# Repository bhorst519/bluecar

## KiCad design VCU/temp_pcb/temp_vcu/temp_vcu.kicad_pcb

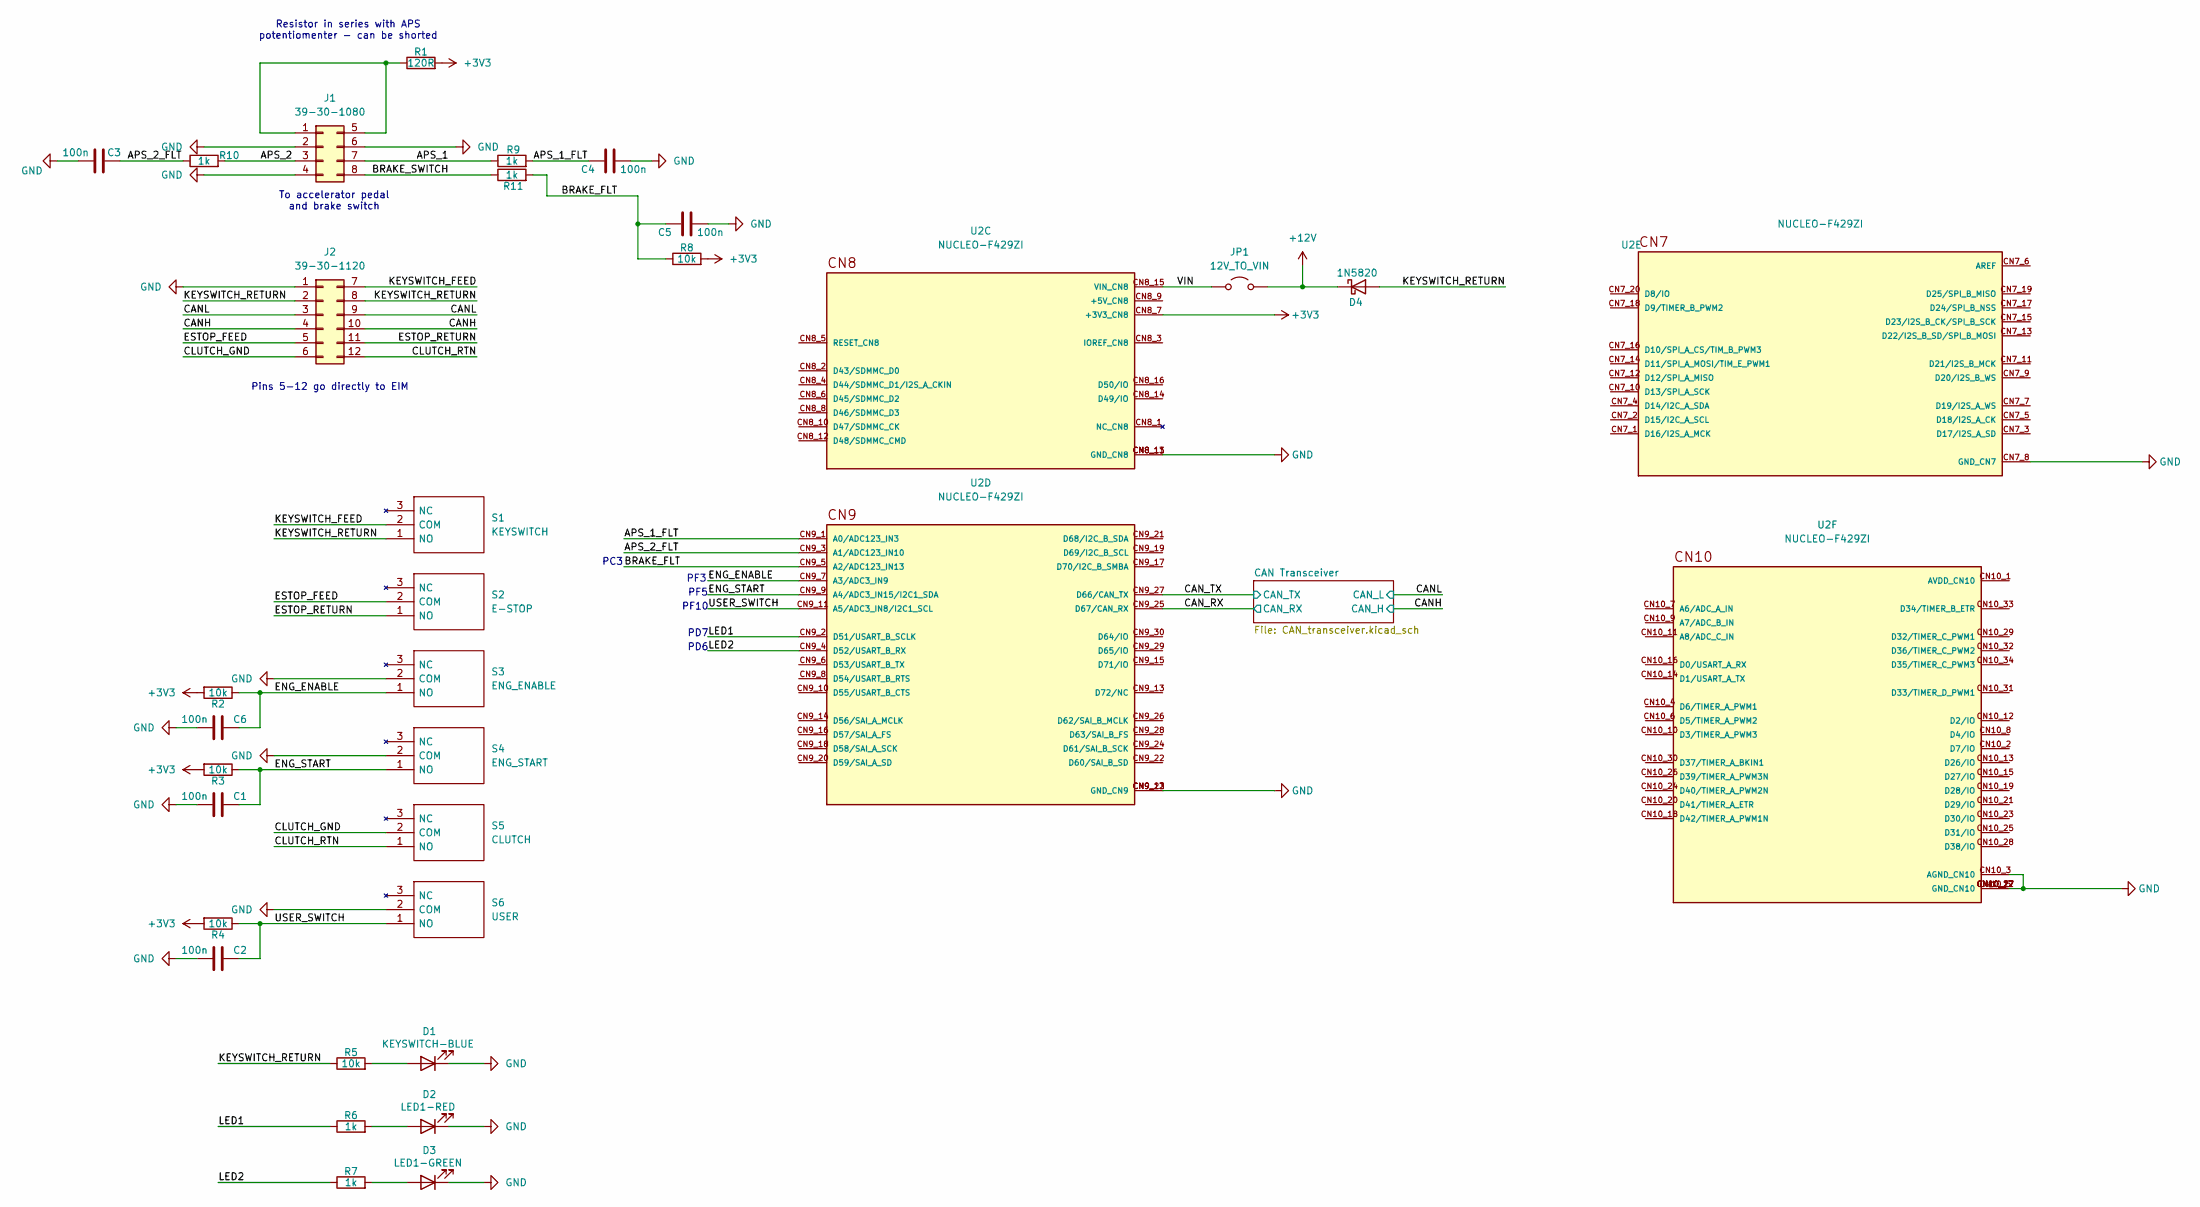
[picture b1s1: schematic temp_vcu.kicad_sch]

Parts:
C1, C2, C3, C4, C5, C6: 100n; C_0805_2012Metric_Pad1.18x1.45mm_HandSolder
D1: KEYSWITCH-BLUE; LED_D4.0mm
D2: LED1-RED; LED_D4.0mm
D3: LED1-GREEN; LED_D4.0mm
D4: 1N5820; D_DO-201AD_P15.24mm_Horizontal
J1: 39-30-1080; Molex_Mini-Fit_Jr_5569-08A2_2x04_P4.20mm_Horizontal
J2: 39-30-1120; Molex_Mini-Fit_Jr_5569-12A2_2x06_P4.20mm_Horizontal
JP1: 12V_TO_VIN; PinHeader_1x02_P2.54mm_Vertical
R1: 120R; R_Axial_DIN0207_L6.3mm_D2.5mm_P10.16mm_Horizontal
R2, R3, R4, R5, R8: 10k; R_Axial_DIN0207_L6.3mm_D2.5mm_P10.16mm_Horizontal
R6, R7, R9, R10, R11: 1k; R_Axial_DIN0207_L6.3mm_D2.5mm_P10.16mm_Horizontal
S1: KEYSWITCH; 2MS1T2B4M2QES; Mouser Part Number 118-2MS1T2B4M2QES
S2: E-STOP; 2MS1T2B4M2QES; Mouser Part Number 118-2MS1T2B4M2QES
S3: ENG_ENABLE; 2MS1T2B4M2QES; Mouser Part Number 118-2MS1T2B4M2QES
S4: ENG_START; 2MS1T2B4M2QES; Mouser Part Number 118-2MS1T2B4M2QES
S5: CLUTCH; 2MS1T2B4M2QES; Mouser Part Number 118-2MS1T2B4M2QES
S6: USER; 2MS1T2B4M2QES; Mouser Part Number 118-2MS1T2B4M2QES
U2: NUCLEO-F429ZI; MODULE_NUCLEO-F429ZI; PARTREV 8

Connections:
+3V3: R1.2, R2.2, R3.2, R4.2, R8.2, U2.CN8_7 (+3V3_CN8); also elsewhere on the board
+12V: D4.1 (K), JP1.2 (B)
/APS_1: J1.7, R9.1
/APS_1_FLT: C4.2, R9.2, U2.CN9_1 (A0/ADC123_IN3)
/APS_2: J1.3, R10.2
/APS_2_FLT: C3.2, R10.1, U2.CN9_3 (A1/ADC123_IN10)
/BRAKE_FLT: C5.2, R8.1, R11.2, U2.CN9_5 (A2/ADC123_IN13)
/BRAKE_SWITCH: J1.8, R11.1
/CANH: J2.4, J2.10; also elsewhere on the board
/CANL: J2.3, J2.9; also elsewhere on the board
/CAN_RX: U2.CN9_25 (D67/CAN_RX); also elsewhere on the board
/CAN_TX: U2.CN9_27 (D66/CAN_TX); also elsewhere on the board
/CLUTCH_GND: J2.6, S5.2 (COM)
/CLUTCH_RTN: J2.12, S5.1 (NO)
/ENG_ENABLE: C6.2, R2.1, S3.1 (NO), U2.CN9_7 (A3/ADC3_IN9)
/ENG_START: C1.2, R3.1, S4.1 (NO), U2.CN9_9 (A4/ADC3_IN15/I2C1_SDA)
/ESTOP_FEED: J2.5, S2.2 (COM)
/ESTOP_RETURN: J2.11, S2.1 (NO)
/KEYSWITCH_FEED: J2.7, S1.2 (COM)
/KEYSWITCH_RETURN: D4.2 (A), J2.2, J2.8, R5.1, S1.1 (NO)
/LED1: R6.1, U2.CN9_2 (D51/USART_B_SCLK)
/LED2: R7.1, U2.CN9_4 (D52/USART_B_RX)
/USER_SWITCH: C2.2, R4.1, S6.1 (NO), U2.CN9_11 (A5/ADC3_IN8/I2C1_SCL)
/VIN: JP1.1 (A), U2.CN8_15 (VIN_CN8)
GND: C1.1, C2.1, C3.1, C4.1, C5.1, C6.1, D1.1 (K), D2.1 (K), D3.1 (K), J1.2, J1.4, J1.6, J2.1, S3.2 (COM), S4.2 (COM), S6.2 (COM), U2.CN7_8 (GND_CN7), U2.CN8_11 (GND_CN8), U2.CN8_13 (GND_CN8), U2.CN9_12 (GND_CN9), U2.CN9_23 (GND_CN9), U2.CN10_3 (AGND_CN10), U2.CN10_5 (GND_CN10), U2.CN10_17 (GND_CN10), U2.CN10_22 (GND_CN10), U2.CN10_27 (GND_CN10); also elsewhere on the board
unnamed: D1.2 (A), R5.2
unnamed: D2.2 (A), R6.2
unnamed: D3.2 (A), R7.2
unnamed: J1.1, J1.5, R1.1

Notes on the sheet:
Resistor in series with APS potentiomenter - can be shorted
PF5
To accelerator pedal and brake switch
PD7
PD6
PF3
PF10
Pins 5-12 go directly to EIM
PC3

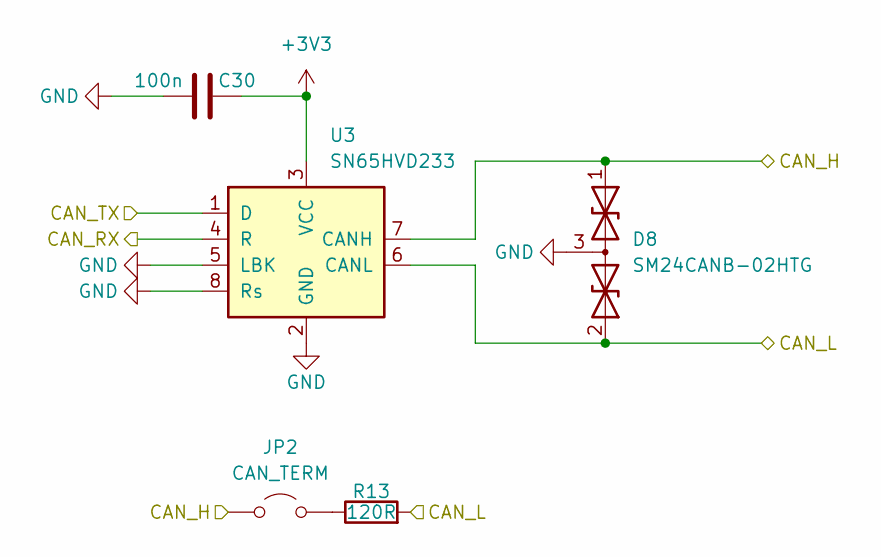
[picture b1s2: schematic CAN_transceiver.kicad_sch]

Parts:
C30: 100n; C_0805_2012Metric_Pad1.18x1.45mm_HandSolder
D8: SM24CANB-02HTG; SOT-23-3
JP2: CAN_TERM; PinHeader_1x02_P2.54mm_Vertical
R13: 120R; R_Axial_DIN0207_L6.3mm_D2.5mm_P10.16mm_Horizontal
U3: SN65HVD233; SOIC-8_3.9x4.9mm_P1.27mm

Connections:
+3V3: C30.2, U3.3 (VCC); also elsewhere on the board
/CANH: D8.1 (A1), JP2.1 (A), U3.7 (CANH); also elsewhere on the board
/CANL: D8.2 (A2), R13.2, U3.6 (CANL); also elsewhere on the board
/CAN_RX: U3.4 (R); also elsewhere on the board
/CAN_TX: U3.1 (D); also elsewhere on the board
GND: C30.1, D8.3 (common), U3.2 (GND), U3.5 (LBK), U3.8 (Rs); also elsewhere on the board
unnamed: JP2.2 (B), R13.1

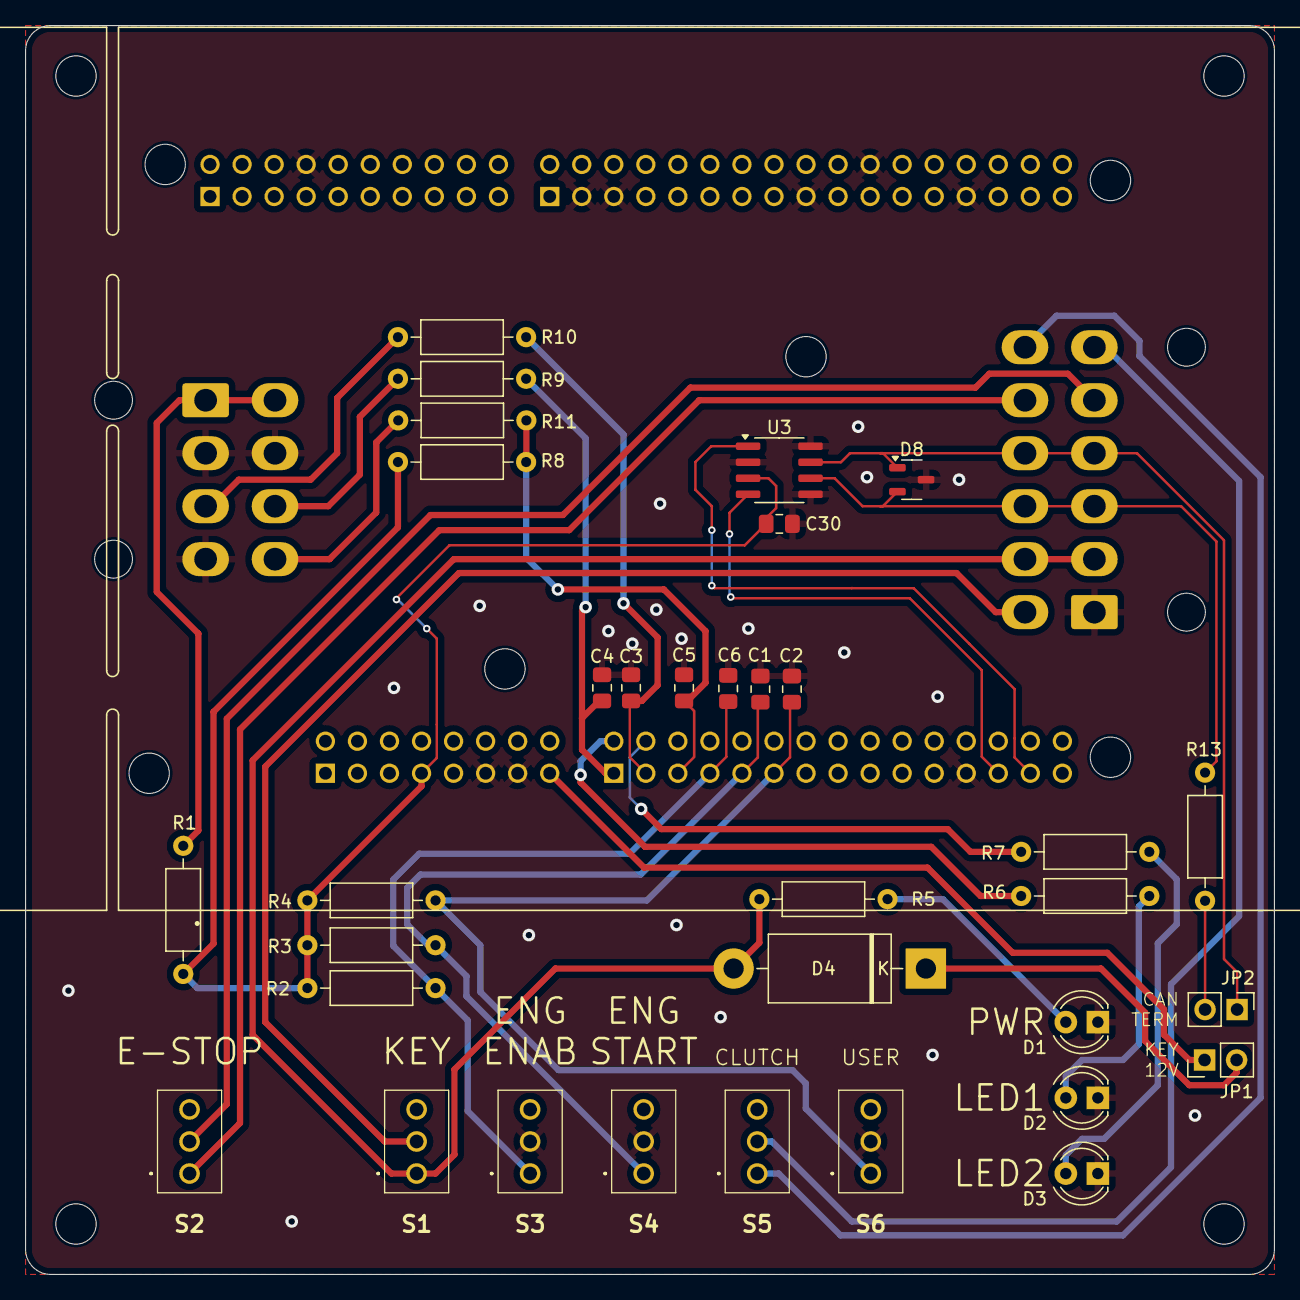
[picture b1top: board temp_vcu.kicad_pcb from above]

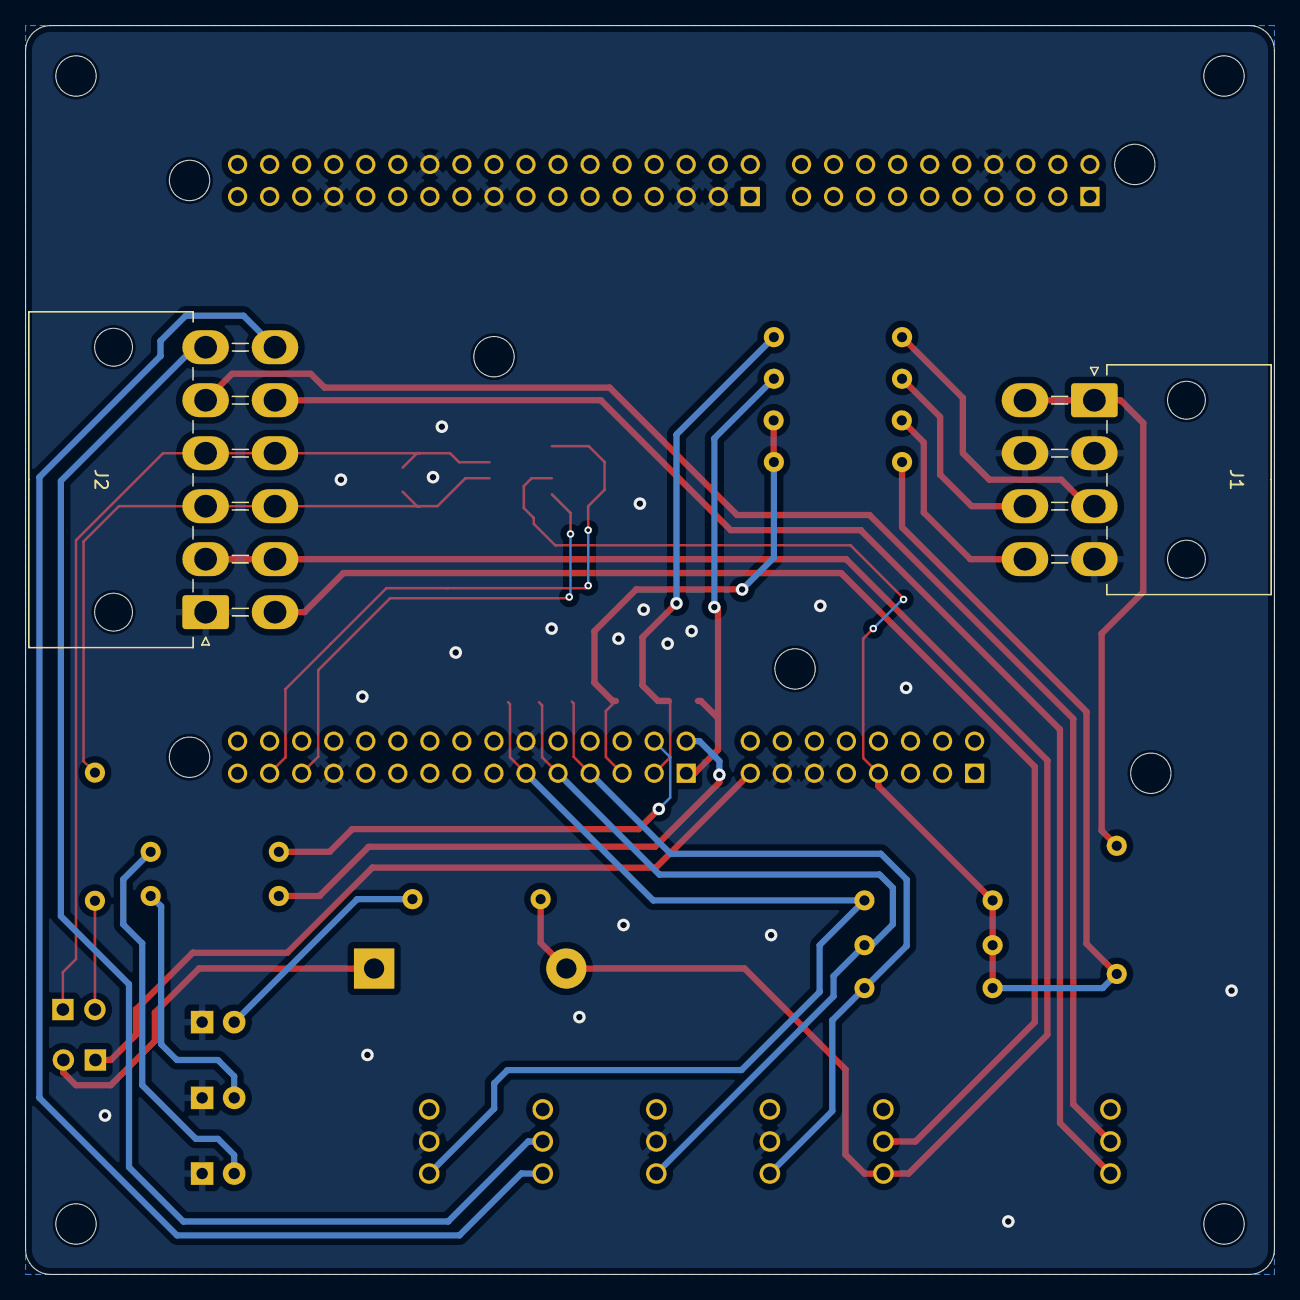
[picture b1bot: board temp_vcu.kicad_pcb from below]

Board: 2 copper layers, 99.0 x 99.0 mm, 36 parts (2 on the bottom side), 30 nets.

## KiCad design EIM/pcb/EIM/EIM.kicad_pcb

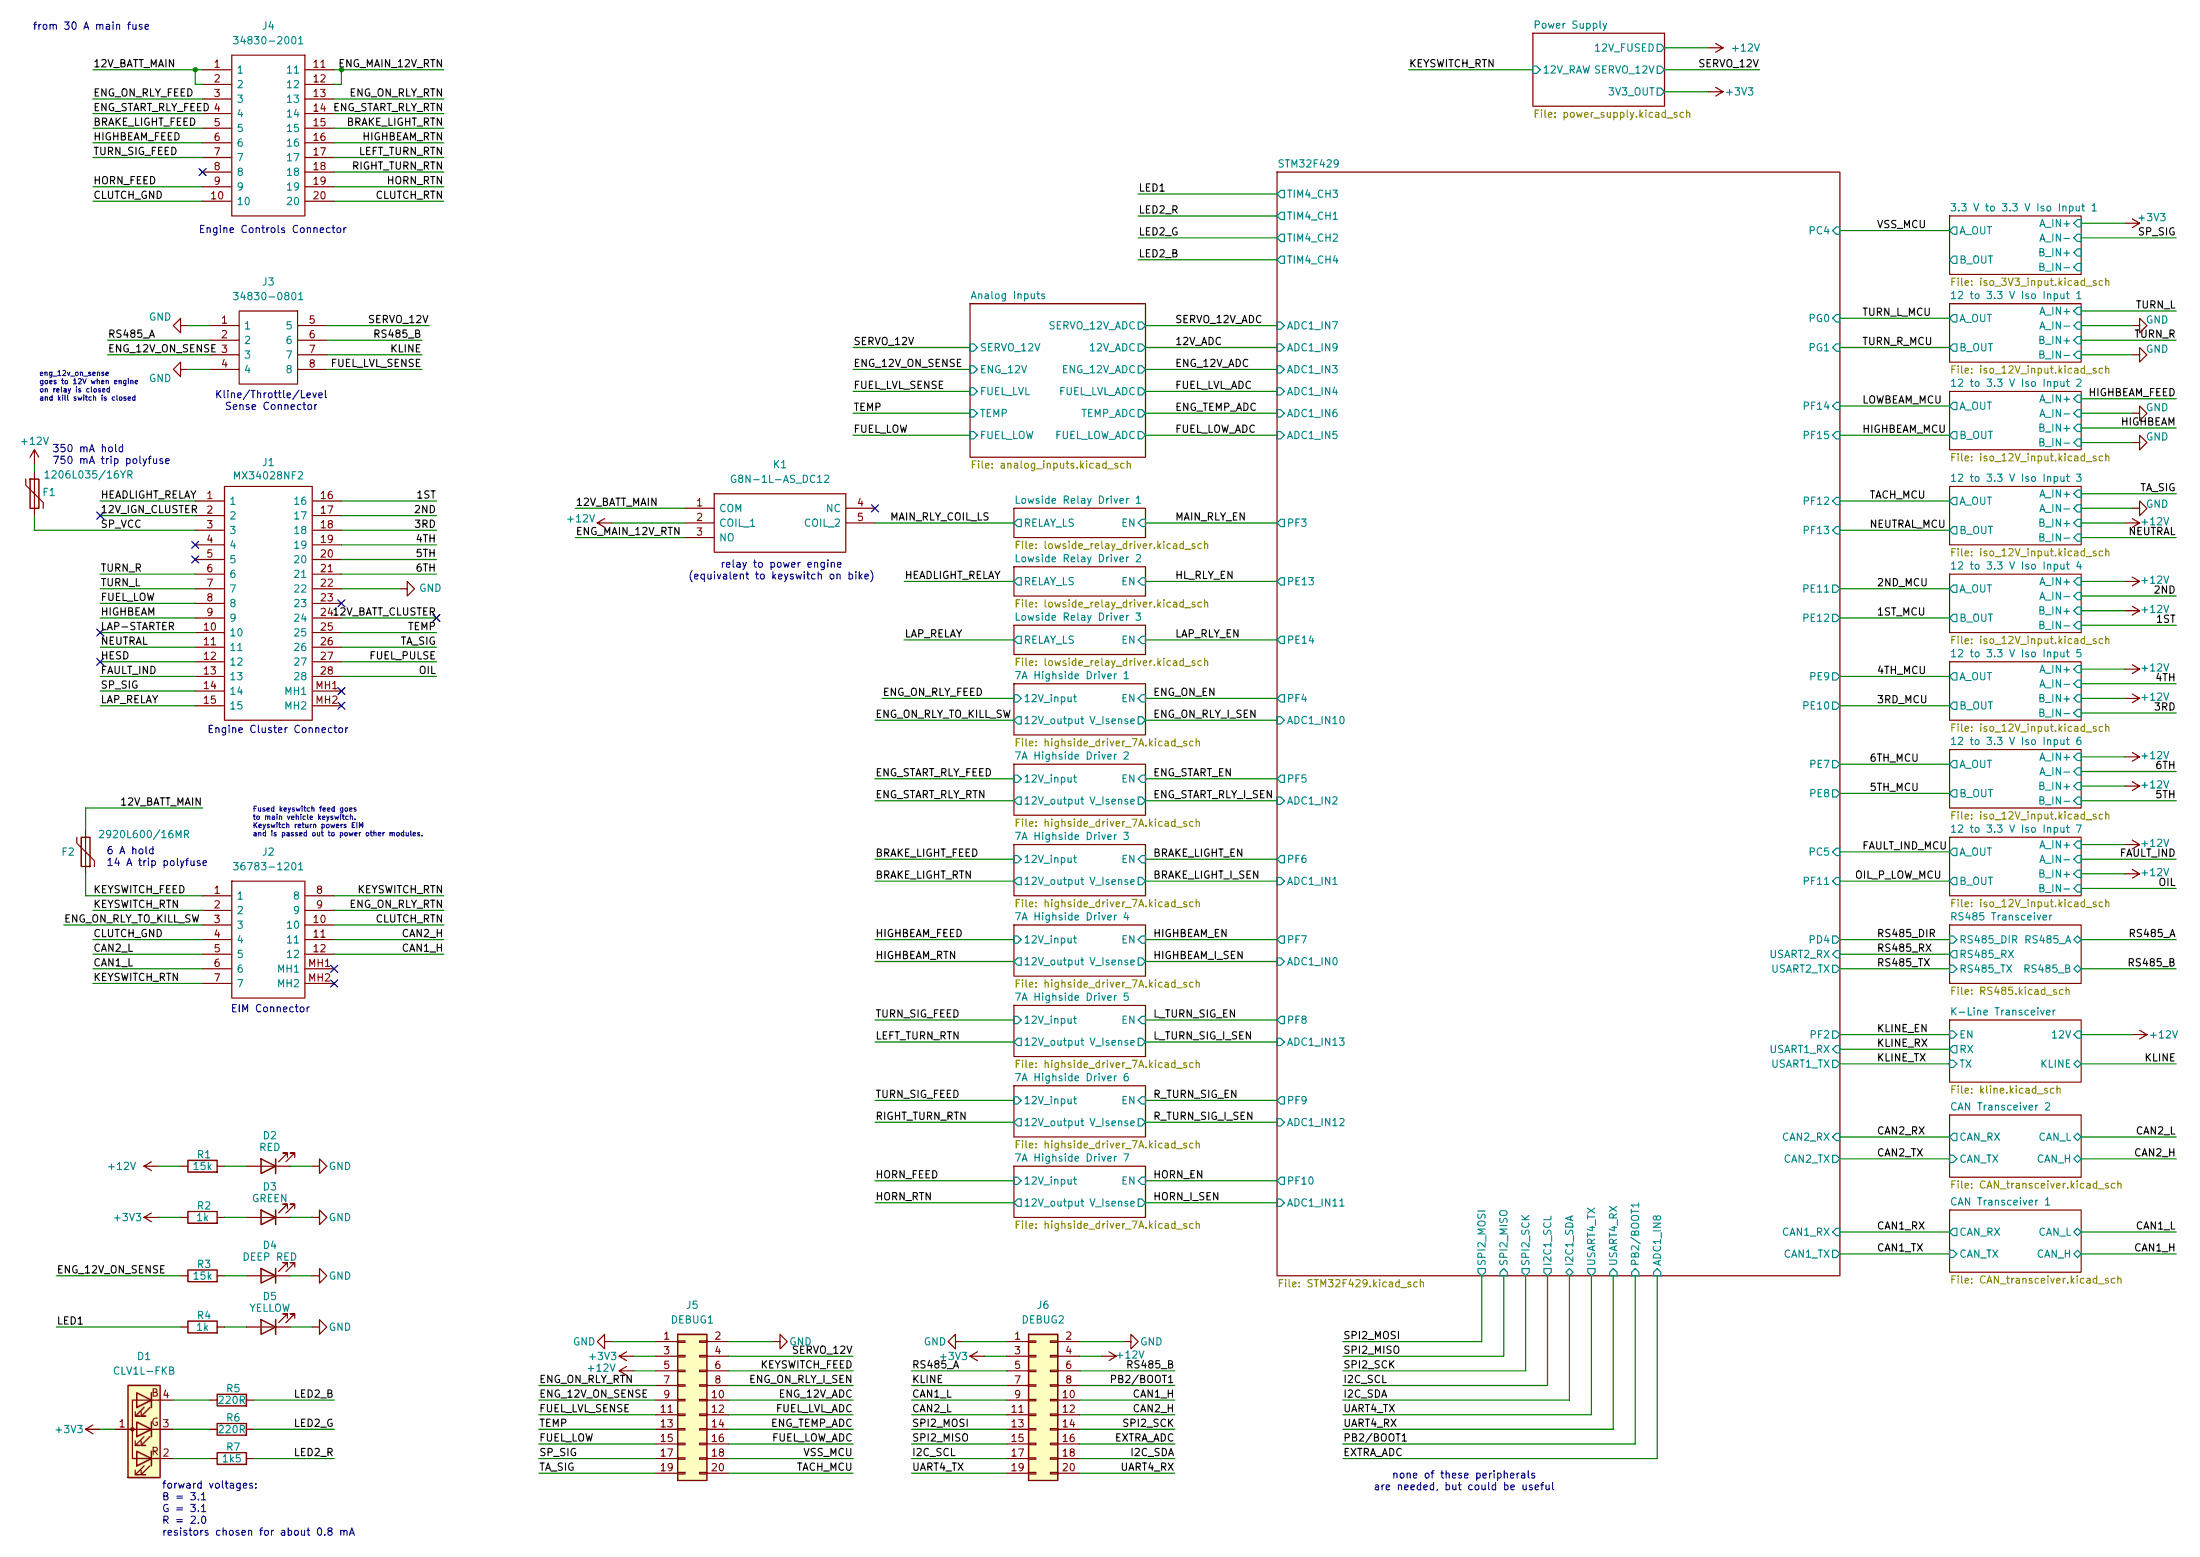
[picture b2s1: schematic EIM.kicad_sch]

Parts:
D1: CLV1L-FKB; LED_Cree-PLCC4_3.2x2.8mm_CCW
D2: RED; LED_0805_2012Metric
D3: GREEN; LED_0805_2012Metric
D4: DEEP RED; LED_0805_2012Metric
D5: YELLOW; LED_0805_2012Metric
F1: 1206L035/16YR; Fuse_1206_3216Metric
F2: 2920L600/16MR; Fuse_2920_7451Metric
J1: MX34028NF2; Mouser Part Number 656-MX34028NF2
J2: 36783-1201; 367831201; Mouser Part Number 538-36783-1201
J3: 34830-0801; 348300801; Mouser Part Number 538-34830-0801
J4: 34830-2001; 348302001; Mouser Part Number 538-34830-2001
J5: DEBUG1; PinHeader_2x10_P2.54mm_Vertical
J6: DEBUG2; PinHeader_2x10_P2.54mm_Vertical
K1: G8N-1L-AS_DC12; G8N1LASDC12; Mouser Part Number 653-G8N-1L-AS-DC12
R1, R3: 15k; R_0805_2012Metric_Pad1.20x1.40mm_HandSolder
R2, R4: 1k; R_0805_2012Metric_Pad1.20x1.40mm_HandSolder
R5, R6: 220R; R_0805_2012Metric_Pad1.20x1.40mm_HandSolder
R7: 1k5; R_0805_2012Metric_Pad1.20x1.40mm_HandSolder

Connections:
+3V3: D1.1 (A), J5.3, J6.3, R2.1; also elsewhere on the board
+12V: F1.1, J5.5, J6.4, K1.2 (COIL_1), R1.1; also elsewhere on the board
/1ST: J1.16; also elsewhere on the board
/2ND: J1.17; also elsewhere on the board
/3RD: J1.18; also elsewhere on the board
/4TH: J1.19; also elsewhere on the board
/5TH: J1.20; also elsewhere on the board
/6TH: J1.21; also elsewhere on the board
/12V_BATT_CLUSTER: J1.24
/12V_BATT_MAIN: F2.2, J4.1, J4.2, K1.1 (COM)
/12V_IGN_CLUSTER: J1.2
/BRAKE_LIGHT_FEED: J4.5; also elsewhere on the board
/BRAKE_LIGHT_RTN: J4.15; also elsewhere on the board
/CAN1_H: J2.12, J6.10; also elsewhere on the board
/CAN1_L: J2.6, J6.9; also elsewhere on the board
/CAN2_H: J2.11, J6.12; also elsewhere on the board
/CAN2_L: J2.5, J6.11; also elsewhere on the board
/CLUTCH_GND: J2.4, J4.10
/CLUTCH_RTN: J2.10, J4.20
/ENG_12V_ADC: J5.10; also elsewhere on the board
/ENG_12V_ON_SENSE: J3.3, J5.9, R3.1; also elsewhere on the board
/ENG_MAIN_12V_RTN: J4.11, J4.12, K1.3 (NO)
/ENG_ON_RLY_FEED: J4.3; also elsewhere on the board
/ENG_ON_RLY_I_SEN: J5.8; also elsewhere on the board
/ENG_ON_RLY_RTN: J2.9, J4.13, J5.7
/ENG_ON_RLY_TO_KILL_SW: J2.3; also elsewhere on the board
/ENG_START_RLY_FEED: J4.4; also elsewhere on the board
/ENG_START_RLY_RTN: J4.14; also elsewhere on the board
/ENG_TEMP_ADC: J5.14; also elsewhere on the board
/EXTRA_ADC: J6.16; also elsewhere on the board
/FAULT_IND: J1.13; also elsewhere on the board
/FUEL_LOW: J1.8, J5.15; also elsewhere on the board
/FUEL_LOW_ADC: J5.16; also elsewhere on the board
/FUEL_LVL_ADC: J5.12; also elsewhere on the board
/FUEL_LVL_SENSE: J3.8, J5.11; also elsewhere on the board
/FUEL_PULSE: J1.27
/HEADLIGHT_RELAY: J1.1; also elsewhere on the board
/HESD: J1.12
/HIGHBEAM: J1.9; also elsewhere on the board
/HIGHBEAM_FEED: J4.6; also elsewhere on the board
/HIGHBEAM_RTN: J4.16; also elsewhere on the board
/HORN_FEED: J4.9; also elsewhere on the board
/HORN_RTN: J4.19; also elsewhere on the board
/I2C_SCL: J6.17; also elsewhere on the board
/I2C_SDA: J6.18; also elsewhere on the board
/KEYSWITCH_FEED: F2.1, J2.1, J5.6
/KEYSWITCH_RTN: J2.2, J2.7, J2.8; also elsewhere on the board
/KLINE: J3.7, J6.7; also elsewhere on the board
/LAP-STARTER: J1.10
/LAP_RELAY: J1.15; also elsewhere on the board
/LED1: R4.1; also elsewhere on the board
/LED2_B: R5.2; also elsewhere on the board
/LED2_G: R6.2; also elsewhere on the board
/LED2_R: R7.2; also elsewhere on the board
/LEFT_TURN_RTN: J4.17; also elsewhere on the board
/MAIN_RLY_COIL_LS: K1.5 (COIL_2); also elsewhere on the board
/NEUTRAL: J1.11; also elsewhere on the board
/OIL: J1.28; also elsewhere on the board
/PB2/BOOT1: J6.8; also elsewhere on the board
/RIGHT_TURN_RTN: J4.18; also elsewhere on the board
/RS485_A: J3.2, J6.5; also elsewhere on the board
/RS485_B: J3.6, J6.6; also elsewhere on the board
/SERVO_12V: J3.5, J5.4; also elsewhere on the board
/SPI2_MISO: J6.15; also elsewhere on the board
/SPI2_MOSI: J6.13; also elsewhere on the board
/SPI2_SCK: J6.14; also elsewhere on the board
/SP_SIG: J1.14, J5.17; also elsewhere on the board
/SP_VCC: F1.2, J1.3
/TACH_MCU: J5.20; also elsewhere on the board
/TA_SIG: J1.26, J5.19; also elsewhere on the board
/TEMP: J1.25, J5.13; also elsewhere on the board
/TURN_L: J1.7; also elsewhere on the board
/TURN_R: J1.6; also elsewhere on the board
/TURN_SIG_FEED: J4.7; also elsewhere on the board
/UART4_RX: J6.20; also elsewhere on the board
/UART4_TX: J6.19; also elsewhere on the board
/VSS_MCU: J5.18; also elsewhere on the board
GND: D2.1 (K), D3.1 (K), D4.1 (K), D5.1 (K), J1.22, J3.1, J3.4, J5.1, J5.2, J6.1, J6.2; also elsewhere on the board
unnamed: D1.4 (BK), R5.1
unnamed: D1.3 (GK), R6.1
unnamed: D1.2 (RK), R7.1
unnamed: D2.2 (A), R1.2
unnamed: D3.2 (A), R2.2
unnamed: D4.2 (A), R3.2
unnamed: D5.2 (A), R4.2

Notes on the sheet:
Fused keyswitch feed goes to main vehicle keyswitch. Keyswitch return powers EIM and is passed out to power other modules.
Kline/Throttle/Level Sense Connector
eng_12v_on_sense goes to 12V when engine on relay is closed and kill switch is closed
from 30 A main fuse
none of these peripherals are needed, but could be useful
relay to power engine (equivalent to keyswitch on bike)
6 A hold 14 A trip polyfuse
forward voltages: B = 3.1 G = 3.1 R = 2.0 resistors chosen for about 0.8 mA
Engine Cluster Connector
Engine Controls Connector
EIM Connector
350 mA hold 750 mA trip polyfuse

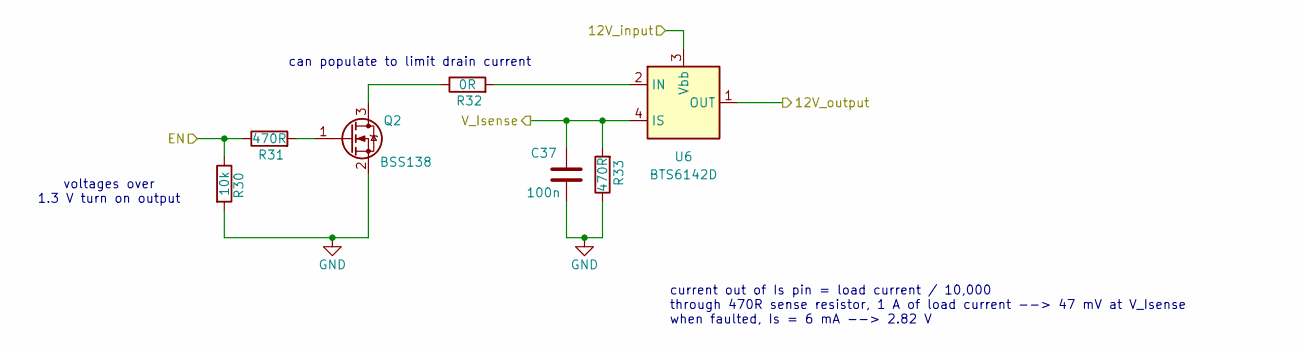
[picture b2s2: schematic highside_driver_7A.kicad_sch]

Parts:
C37: 100n; C_0805_2012Metric_Pad1.18x1.45mm_HandSolder
Q2: BSS138; SOT-23
R30: 10k; R_0805_2012Metric_Pad1.20x1.40mm_HandSolder
R31, R33: 470R; R_0805_2012Metric_Pad1.20x1.40mm_HandSolder
R32: 0R; R_0805_2012Metric_Pad1.20x1.40mm_HandSolder
U6: BTS6142D; TO-252-4

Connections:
/ENG_START_EN: R30.1, R31.1; also elsewhere on the board
/ENG_START_RLY_FEED: U6.3 (Vbb); also elsewhere on the board
/ENG_START_RLY_I_SEN: C37.2, R33.2, U6.4 (IS); also elsewhere on the board
/ENG_START_RLY_RTN: U6.1 (OUT), U6.5 (OUT); also elsewhere on the board
GND: C37.1, Q2.2 (S), R30.2, R33.1; also elsewhere on the board
unnamed: Q2.3 (D), R32.1
unnamed: Q2.1 (G), R31.2
unnamed: R32.2, U6.2 (IN)

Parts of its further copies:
C36, C38, C39, C40, C41, C42: 100n; C_0805_2012Metric_Pad1.18x1.45mm_HandSolder
Q1, Q3, Q4, Q5, Q6, Q7: BSS138; SOT-23
R26, R34, R38, R42, R46, R50: 10k; R_0805_2012Metric_Pad1.20x1.40mm_HandSolder
R27, R29, R35, R37, R39, R41, R43, R45, R47, R49, R51, R53: 470R; R_0805_2012Metric_Pad1.20x1.40mm_HandSolder
R28, R36, R40, R44, R48, R52: 0R; R_0805_2012Metric_Pad1.20x1.40mm_HandSolder
U5, U7, U8, U9, U10, U11: BTS6142D; TO-252-4

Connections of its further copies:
/BRAKE_LIGHT_EN: R34.1, R35.1; also elsewhere on the board
/BRAKE_LIGHT_FEED: U7.3 (Vbb); also elsewhere on the board
/BRAKE_LIGHT_I_SEN: C38.2, R37.2, U7.4 (IS); also elsewhere on the board
/BRAKE_LIGHT_RTN: U7.1 (OUT), U7.5 (OUT); also elsewhere on the board
/ENG_ON_EN: R26.1, R27.1; also elsewhere on the board
/ENG_ON_RLY_FEED: U5.3 (Vbb); also elsewhere on the board
/ENG_ON_RLY_I_SEN: C36.2, R29.2, U5.4 (IS); also elsewhere on the board
/ENG_ON_RLY_TO_KILL_SW: U5.1 (OUT), U5.5 (OUT); also elsewhere on the board
/HIGHBEAM_EN: R38.1, R39.1; also elsewhere on the board
/HIGHBEAM_FEED: U8.3 (Vbb); also elsewhere on the board
/HIGHBEAM_I_SEN: C39.2, R41.2, U8.4 (IS); also elsewhere on the board
/HIGHBEAM_RTN: U8.1 (OUT), U8.5 (OUT); also elsewhere on the board
/HORN_EN: R50.1, R51.1; also elsewhere on the board
/HORN_FEED: U11.3 (Vbb); also elsewhere on the board
/HORN_I_SEN: C42.2, R53.2, U11.4 (IS); also elsewhere on the board
/HORN_RTN: U11.1 (OUT), U11.5 (OUT); also elsewhere on the board
/LEFT_TURN_RTN: U9.1 (OUT), U9.5 (OUT); also elsewhere on the board
/L_TURN_SIG_EN: R42.1, R43.1; also elsewhere on the board
/L_TURN_SIG_I_SEN: C40.2, R45.2, U9.4 (IS); also elsewhere on the board
/RIGHT_TURN_RTN: U10.1 (OUT), U10.5 (OUT); also elsewhere on the board
/R_TURN_SIG_EN: R46.1, R47.1; also elsewhere on the board
/R_TURN_SIG_I_SEN: C41.2, R49.2, U10.4 (IS); also elsewhere on the board
/TURN_SIG_FEED: U9.3 (Vbb), U10.3 (Vbb); also elsewhere on the board
GND: C36.1, C38.1, C39.1, C40.1, C41.1, C42.1, Q1.2 (S), Q3.2 (S), Q4.2 (S), Q5.2 (S), Q6.2 (S), Q7.2 (S), R26.2, R29.1, R34.2, R37.1, R38.2, R41.1, R42.2, R45.1, R46.2, R49.1, R50.2, R53.1; also elsewhere on the board
unnamed: Q1.3 (D), R28.1
unnamed: Q1.1 (G), R27.2
unnamed: Q3.3 (D), R36.1
unnamed: Q3.1 (G), R35.2
unnamed: Q4.3 (D), R40.1
unnamed: Q4.1 (G), R39.2
unnamed: Q5.3 (D), R44.1
unnamed: Q5.1 (G), R43.2
unnamed: Q6.3 (D), R48.1
unnamed: Q6.1 (G), R47.2
unnamed: Q7.3 (D), R52.1
unnamed: Q7.1 (G), R51.2
unnamed: R28.2, U5.2 (IN)
unnamed: R36.2, U7.2 (IN)
unnamed: R40.2, U8.2 (IN)
unnamed: R44.2, U9.2 (IN)
unnamed: R48.2, U10.2 (IN)
unnamed: R52.2, U11.2 (IN)

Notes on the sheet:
voltages over 1.3 V turn on output
current out of Is pin = load current / 10,000 through 470R sense resistor, 1 A of load current --> 47 mV at V_Isense when faulted, Is = 6 mA --> 2.82 V
can populate to limit drain current

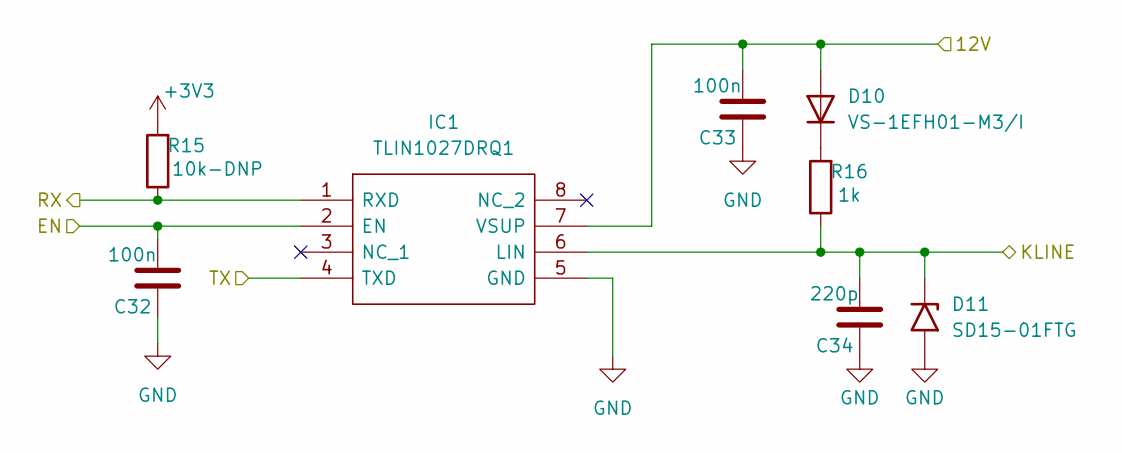
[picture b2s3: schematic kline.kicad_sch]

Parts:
C32, C33: 100n; C_0805_2012Metric_Pad1.18x1.45mm_HandSolder
C34: 220p; C_0805_2012Metric_Pad1.18x1.45mm_HandSolder
D10: VS-1EFH01-M3/I; D_SMF
D11: SD15-01FTG; D_SOD-323
IC1: TLIN1027DRQ1; SOIC-8_3.9x4.9mm_P1.27mm; Manufacturer_Part_Number TLIN1027DRQ1
R15: 10k-DNP; R_0805_2012Metric_Pad1.20x1.40mm_HandSolder
R16: 1k; R_0805_2012Metric_Pad1.20x1.40mm_HandSolder

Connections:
+3V3: R15.2; also elsewhere on the board
+12V: C33.1, D10.2 (A), IC1.7 (VSUP); also elsewhere on the board
/KLINE: C34.1, D11.1 (A1), IC1.6 (LIN), R16.1; also elsewhere on the board
/KLINE_EN: C32.1, IC1.2 (EN); also elsewhere on the board
/KLINE_RX: IC1.1 (RXD), R15.1; also elsewhere on the board
/KLINE_TX: IC1.4 (TXD); also elsewhere on the board
GND: C32.2, C33.2, C34.2, D11.2 (A2), IC1.5 (GND); also elsewhere on the board
unnamed: D10.1 (K), R16.2

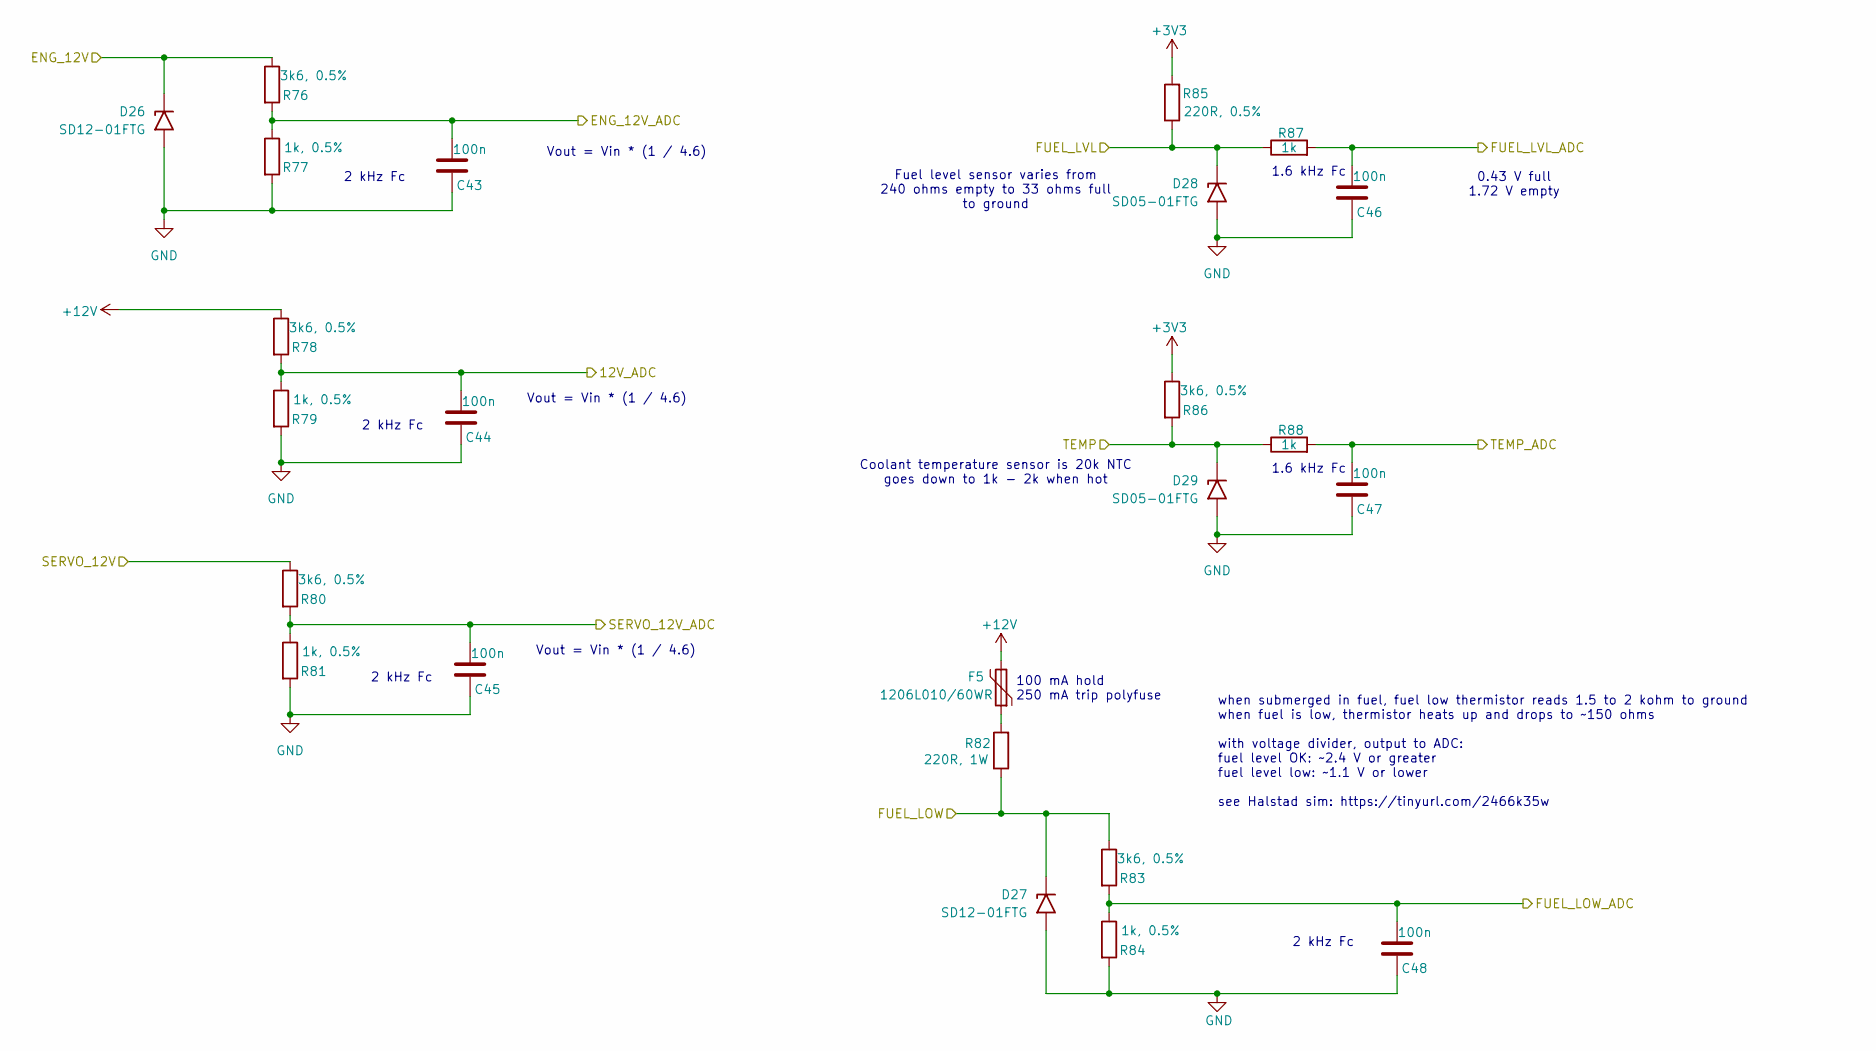
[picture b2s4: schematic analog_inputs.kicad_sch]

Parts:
C43, C44, C45, C46, C47, C48: 100n; C_0805_2012Metric_Pad1.18x1.45mm_HandSolder
D26, D27: SD12-01FTG; D_SOD-323
D28, D29: SD05-01FTG; D_SOD-323
F5: 1206L010/60WR; Fuse_1206_3216Metric
R76, R78, R80, R83, R86: 3k6, 0.5%; R_0805_2012Metric_Pad1.20x1.40mm_HandSolder
R77, R79, R81, R84: 1k, 0.5%; R_0805_2012Metric_Pad1.20x1.40mm_HandSolder
R82: 220R, 1W; R_2512_6332Metric
R85: 220R, 0.5%; R_0805_2012Metric_Pad1.20x1.40mm_HandSolder
R87, R88: 1k; R_0805_2012Metric_Pad1.20x1.40mm_HandSolder

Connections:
+3V3: R85.2, R86.1; also elsewhere on the board
+12V: F5.2, R78.1; also elsewhere on the board
/12V_ADC: C44.1, R78.2, R79.1; also elsewhere on the board
/ENG_12V_ADC: C43.1, R76.2, R77.1; also elsewhere on the board
/ENG_12V_ON_SENSE: D26.1 (A1), R76.1; also elsewhere on the board
/ENG_TEMP_ADC: C47.1, R88.2; also elsewhere on the board
/FUEL_LOW: D27.1 (A1), R82.1, R83.1; also elsewhere on the board
/FUEL_LOW_ADC: C48.1, R83.2, R84.1; also elsewhere on the board
/FUEL_LVL_ADC: C46.1, R87.2; also elsewhere on the board
/FUEL_LVL_SENSE: D28.1 (A1), R85.1, R87.1; also elsewhere on the board
/SERVO_12V: R80.1; also elsewhere on the board
/SERVO_12V_ADC: C45.1, R80.2, R81.1; also elsewhere on the board
/TEMP: D29.1 (A1), R86.2, R88.1; also elsewhere on the board
GND: C43.2, C44.2, C45.2, C46.2, C47.2, C48.2, D26.2 (A2), D27.2 (A2), D28.2 (A2), D29.2 (A2), R77.2, R79.2, R81.2, R84.2; also elsewhere on the board
unnamed: F5.1, R82.2

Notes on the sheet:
2 kHz Fc
Vout = Vin * (1 / 4.6)
1.6 kHz Fc
0.43 V full 1.72 V empty
Coolant temperature sensor is 20k NTC goes down to 1k - 2k when hot
when submerged in fuel, fuel low thermistor reads 1.5 to 2 kohm to ground when fuel is low, thermistor heats up and drops to ~150 ohms with voltage divider, output to ADC: fuel level OK: ~2.4 V or greater fuel level low: ~1.1 V or lower see Halstad sim: https://tinyurl.com/2466k35w
Fuel level sensor varies from 240 ohms empty to 33 ohms full to ground
100 mA hold 250 mA trip polyfuse
